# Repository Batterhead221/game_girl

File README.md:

# game_girl

GAME GIRL is a custom ESP32-S3 handheld mini-arcade built around a monochrome OLED display, rotary encoder controls, button input, buzzer audio, and battery support. AKA a handheld controlable tamagotchi like digital pet that I made for my niece.

## Features
- Custom PCB designed in KiCad
- ESP32-S3 based handheld platform
- 128x64 I2C OLED display
- Rotary encoder + push switch input
- Main action button
- Active buzzer audio
- Soft sleep mode
- Original mini-games:
  - Dress Up
  - Pocket Pet

## Hardware
- ESP32-S3 module
- 128x64 OLED
- Rotary encoder
- Pushbutton
- Active buzzer with transistor driver
- Single-cell LiPo support

## Firmware
The firmware is written in Arduino/C++ and organized as a menu-driven state machine. The device includes a launcher menu, game states, UI rendering, sound feedback, and long-press sleep behavior for handheld use.

## Engineering Highlights
- Built a complete handheld embedded system from schematic to assembled PCB
- Designed a compact display-based UI for limited-resolution hardware
- Implemented encoder and button-driven navigation across multiple games
- Added battery-friendly soft sleep behavior
- Debugged hardware bring-up issues including buzzer driver behavior and real-world encoder handling

## Challenges and Fixes
One of the main bring-up issues was the buzzer driver stage. The buzzer itself tested correctly, but in-circuit debugging showed the low-side transistor stage was not pulling the buzzer node low enough. After tracing the behavior with meter checks and signal testing, the emitter path was corrected to achieve proper switching. I also iterated on encoder handling to make gameplay and menu control more usable with a mechanical rotary input.

## Status
Working prototype. Core hardware and firmware are functional, with several improvements identified for a future board revision.

Next rev will be more compact, "kid friendly" and "prettier"

Designed & Engineered by Brandon Shelly

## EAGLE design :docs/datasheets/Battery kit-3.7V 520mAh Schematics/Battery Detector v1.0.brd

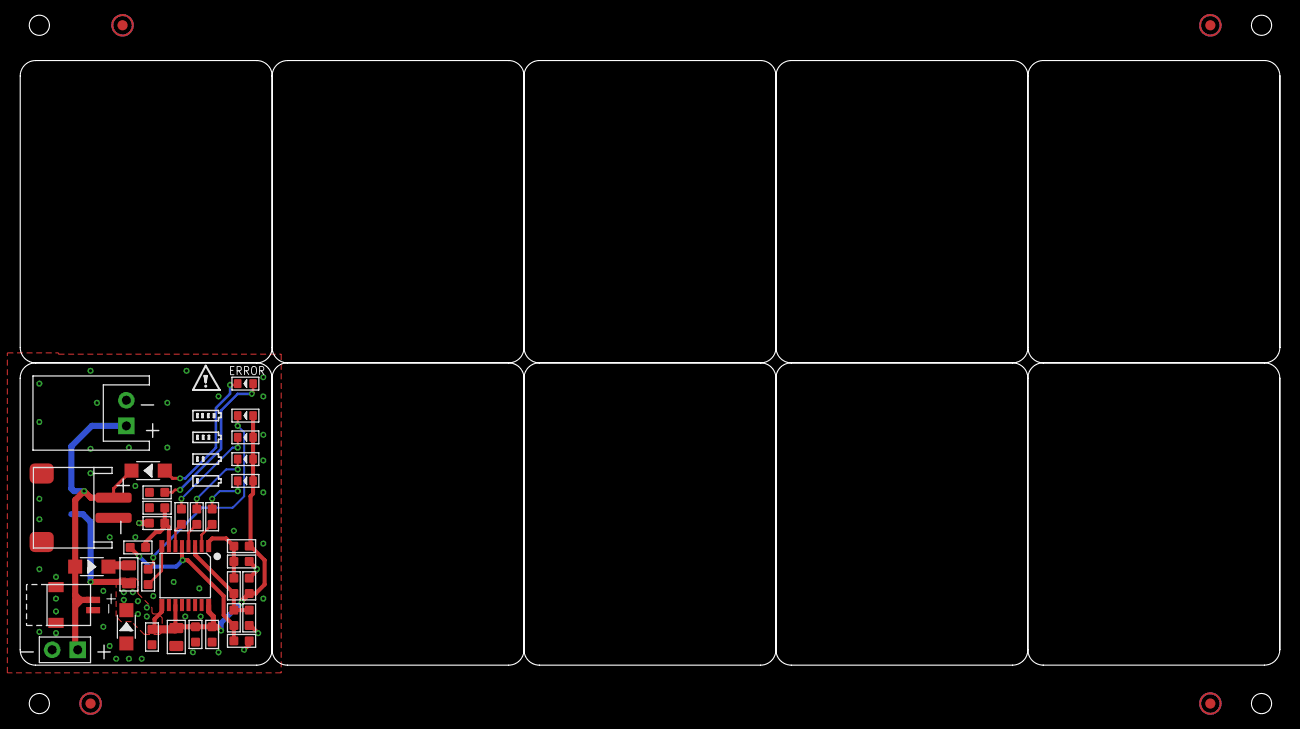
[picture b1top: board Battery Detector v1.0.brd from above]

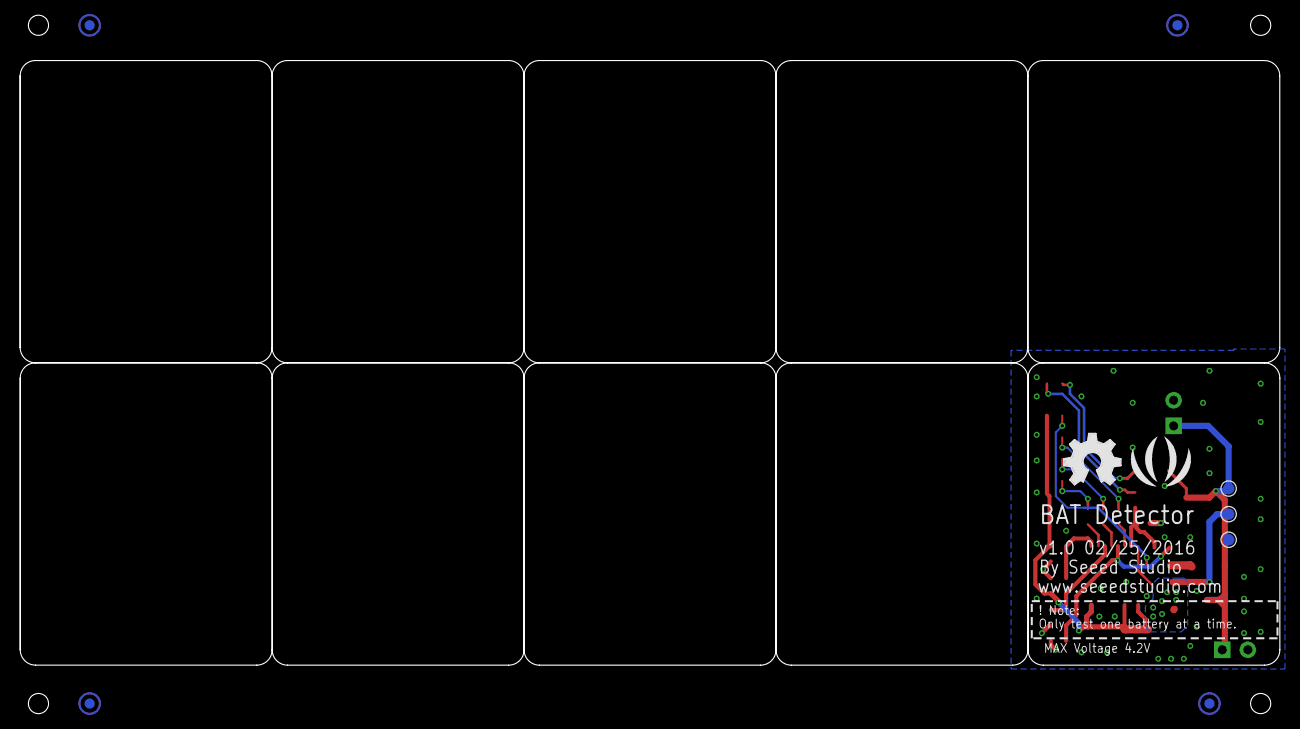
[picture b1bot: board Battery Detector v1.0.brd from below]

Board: 2 copper layers, 125.0 x 60.0 mm, 48 parts (9 on the bottom side), 18 nets.

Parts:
C1, C5, C6, C7, C8, C9: DNP; C0603
C2, C4: 100nF; C0603
C3: 10uF; C0805
D1, D2, D3, D4: Green; LED-0603
D6, D7: B5819W; SOD-123
D8: MMSZ4689; SOD-123
ERROR: RED; LED-0603
FR1, FR2: SEEEDSTUDIO-PCB-FRAME
J1: JST-2P-SMD'1.0; HW2-SMD-1.0-90D
J2: JST-2P-SMD'2.0; HW2-SMD-2.0-90D
J3: JST-2P-DIP'2.54/90D'; JST2-2.54-90D
J4: DNP; H2-2.54
P1, P2, P3, P4, P5, P6, P7, P8: ROUND-MARK-1.0
R1: 430k; R0603
R2: 22k; R0603
R3: 15k; R0603
R4: 18k; R0603
R5: 270k; R0603
R6, R7, R8, R9: 510R; R0603
R10: 1k; R0603
R11: 22R; R0805
TP1, TP2, TP3: DNP; TP-D45MIL
U1: CN1185; TSSOP16-0.65-5X4.4MM
U$7: SEEED-SILK-280*268MIL
U$8: OSHW_FILLX200_NOTEXT

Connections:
GND: C1.1, C2.1, C3.2, C4.1, C5.1, C6.1, C7.1, C8.1, C9.1, D8.+, J1.3, J1.4, J1.-, J2.3, J2.4, J2.-, J3.-, J4.2, R5.1, R10.2, TP2.T, U1.12, U1.13, U1.14
unnamed: R7.1, U1.6
unnamed: D6.-, R11.2
unnamed: C6.2, R1.1, R2.2, U1.1
unnamed: C7.2, R2.1, R3.2, U1.3
unnamed: C8.2, R3.1, R4.2, U1.5
unnamed: R9.1, U1.2
unnamed: R6.1, U1.4
unnamed: R8.1, U1.8
unnamed: D6.+, D7.-, J1.+, J2.+, J3.+, J4.1, TP1.T
unnamed: D1.-, R9.2
unnamed: C9.2, R4.1, R5.2, U1.7
unnamed: D2.-, R6.2
unnamed: D3.-, R7.2
unnamed: D4.-, R8.2
unnamed: ERROR.+, R10.1
unnamed: D7.+, ERROR.-
VCC: C1.2, C2.2, C3.1, C4.2, C5.2, D1.+, D2.+, D3.+, D4.+, D8.-, R1.2, R11.1, TP3.T, U1.9, U1.11, U1.16

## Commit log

2026-04-18 file path restructure
2026-05-03 folder restructure
2026-05-13 Revised repo

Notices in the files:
parts and their libraries:
moudle-new: This work is licensed under the Creative Commons Attribution 4.0 International License.
To view a copy of this license,visit:
http://creativecommons.org/licenses/by-sa/4.0
